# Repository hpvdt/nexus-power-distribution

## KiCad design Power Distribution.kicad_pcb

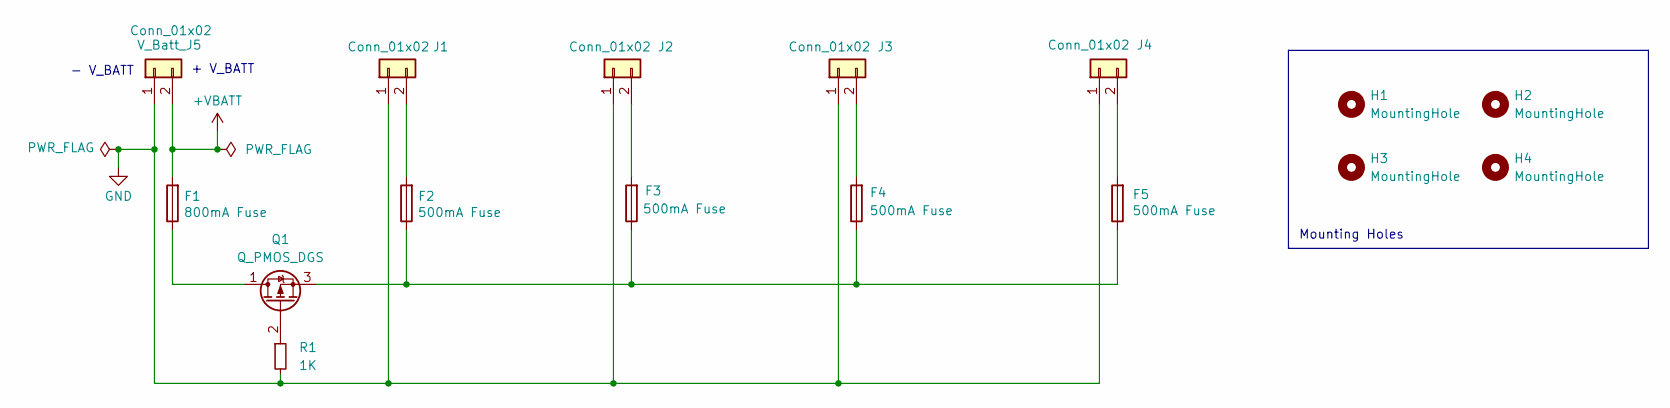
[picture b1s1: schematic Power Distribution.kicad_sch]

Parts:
F1: 800mA Fuse; Fuse_0805_2012Metric
F2, F3, F4, F5: 500mA Fuse; Fuse_0805_2012Metric
H1, H2, H3, H4: MountingHole; MountingHole_3.2mm_M3
J1, J2, J3, J4: Conn_01x02; JST_XH_B2B-XH-A_1x02_P2.50mm_Vertical
Q1: Q_PMOS_DGS; SOT91P240X110-3N
R1: 1K; R_0805_2012Metric
V_Batt_J5: Conn_01x02; JST_XH_B2B-XH-A_1x02_P2.50mm_Vertical

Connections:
+VBATT: F1.2, V_Batt_J5.2
GND: J1.1, J2.1, J3.1, J4.1, R1.2, V_Batt_J5.1
unnamed: F2.2, J1.2
unnamed: F3.2, J2.2
unnamed: F4.2, J3.2
unnamed: F5.2, J4.2
unnamed: F1.1, Q1.1 (D)
unnamed: Q1.2 (G), R1.1
unnamed: F2.1, F3.1, F4.1, F5.1, Q1.3 (S)

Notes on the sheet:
+ V_BATT
Mounting Holes
- V_BATT

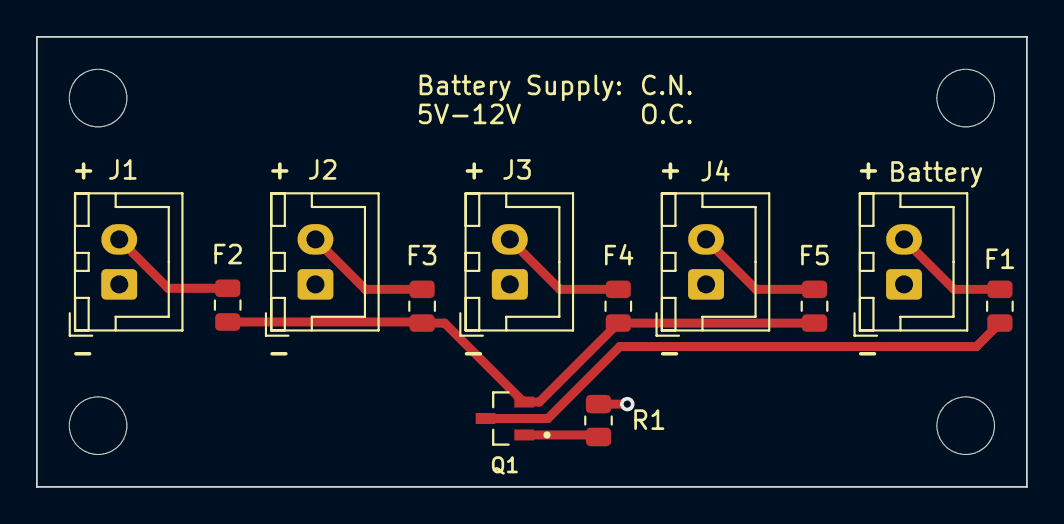
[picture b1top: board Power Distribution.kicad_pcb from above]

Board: 2 copper layers, 55.0 x 25.0 mm, 16 parts (0 on the bottom side), 9 nets.

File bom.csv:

Designator,Footprint,Quantity,Value,LCSC Part #
F1,0805,1,800mA Fuse,
"F2, F3, F4, F5",0805,4,500mA Fuse,
"H1, H2, H3, H4",MountingHole_3.2mm_M3,4,MountingHole,
"J1, J2, J3, J4, V_BATT_J5",JST_XH_B2B-XH-A_1x02_P2.50mm_Vertical,5,Conn_01x02,
Q1,SOT91P240X110-3N,1,Q_PMOS_DGS,
R1,0805,1,1K,

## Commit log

2025-07-29 Add files via upload
    Changed some traces to adhere to new MOSFET footprint (from web library) and meet 0.3mm distance between all components. Addeed Gerber files.
